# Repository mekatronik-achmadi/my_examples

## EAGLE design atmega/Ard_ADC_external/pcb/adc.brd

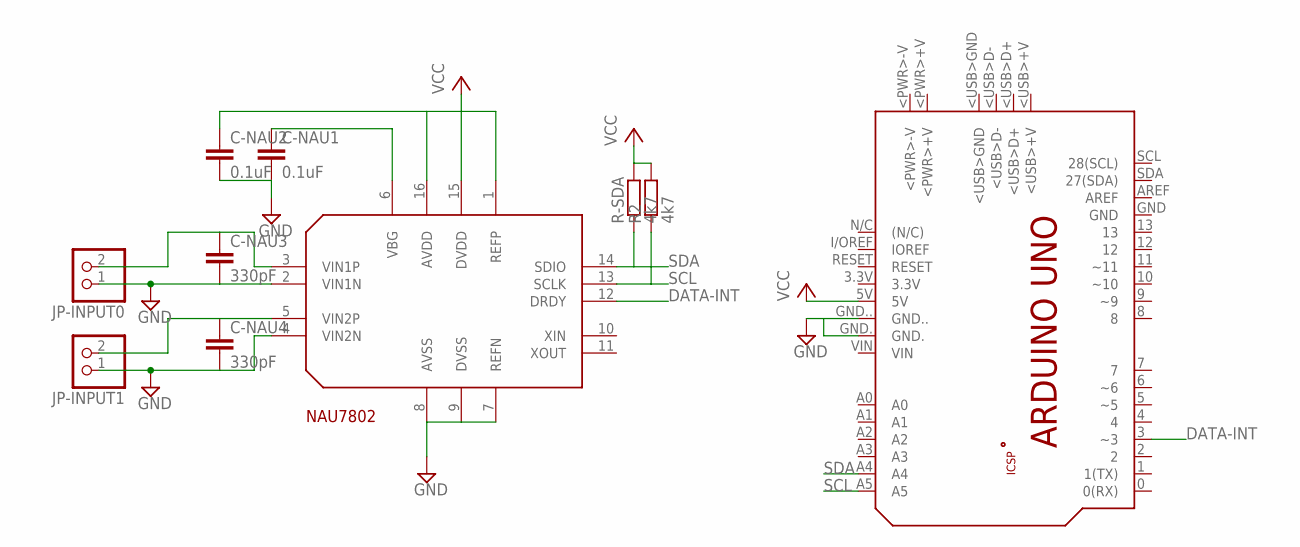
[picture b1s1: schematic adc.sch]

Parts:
C-NAU1, C-NAU2: 0.1uF; C050-024X044
C-NAU3, C-NAU4: 330pF; C050-024X044
JP-INPUT0, JP-INPUT1: PINHD-1X2; 1X02
PCB1: ARDUINO_UNO
R2: 4k7; 0204/7
R-SDA: 4k7; 0204/7
U$1: NAU7802_DIP; DIP16

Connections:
DATA-INT: PCB1.3 (~3), U$1.12 (DRDY)
GND: C-NAU1.2, C-NAU2.2, C-NAU3.2, C-NAU4.2, JP-INPUT0.1, JP-INPUT1.1, PCB1.GND., PCB1.GND.., U$1.2 (VIN1N), U$1.4 (VIN2N), U$1.7 (REFN), U$1.8 (AVSS), U$1.9 (DVSS)
unnamed: C-NAU1.1, U$1.6 (VBG)
unnamed: C-NAU3.1, JP-INPUT0.2, U$1.3 (VIN1P)
unnamed: C-NAU4.1, JP-INPUT1.2, U$1.5 (VIN2P)
SCL: PCB1.A5, R2.1, U$1.13 (SCLK)
SDA: PCB1.A4, R-SDA.1, U$1.14 (SDIO)
VCC: C-NAU2.1, PCB1.5V, R2.2, R-SDA.2, U$1.1 (REFP), U$1.15 (DVDD), U$1.16 (AVDD)

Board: 2 copper layers, 10 parts (0 on the bottom side), 8 nets, no tracks yet.

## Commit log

2018-10-09 some of my examples
2018-10-14 examples stm32 from rtm7777
2018-10-17 lcd library
2018-10-18 java android example
2018-10-20 Java Swing GUI example
2018-10-20 simple SysInfo on Java and Python
2018-10-22 java sysinfo
2018-10-23 blogspot template
2018-10-23 BT Serial Terminal
2018-10-23 gui example (Java and Qt)
2018-10-23 update examples
2018-10-30 document build helper scripts
2018-10-30 more doxygen config
2018-10-30 move to achmadi-default
2018-11-01 Fuzzy in C
2018-11-09 bashrc
2018-11-09 bashrc git
2018-11-10 some java and gtk examples
2018-11-13 mfc example
2018-11-18 win32 api
2018-11-18 win32 c example
2018-11-18 winegcc
2018-11-21 wine32 sys info
2018-11-21 win32 c
2018-11-21 win32 makefile
2018-11-22 win32 c and clean-up
2018-12-13 mingw makefile
2018-12-13 simulasi Fuzzy
2018-12-15 atmega mux
2018-12-17 stm32f103 web
2018-12-17 info, license, and documentation
2018-12-17 add gyro/accel
2018-12-17 rongsokan jalan
2018-12-18 jalan cuyy
2018-12-18 stm32 web mpu6050 prototype
2018-12-19 vector magnitude
2018-12-19 documentation using doxygen
2018-12-19 app copyright
2018-12-19 didin asu
2018-12-20 python ThorlabsPM100
2018-12-20 running as expected
2018-12-25 progress didin
2019-01-20 update WebADC
2019-03-18 re-use anbox
2019-03-21 lcd rpm
2019-03-26 ATMega Basic
2019-03-26 Makefile multi-platform
2019-03-27 basic ATMega examples
2019-03-27 No Simulide example
2019-03-31 on other lib
2019-03-31 face recog opencv
2019-03-31 face recoc opencv-python
2019-04-01 haarcascade flexible
2019-04-05 sim_proteus
2019-04-19 atmegaArduinoRPM
2019-04-21 face_rec analisa
2019-04-21 input capture
2019-04-21 period
2019-06-26 matlab batch run example
2019-07-03 deboat MIUI-10 scripts
2019-07-19 archived Face Recog Job
2019-07-19 example tiny sys-info
2019-07-19 development
2019-07-19 sh_info
2019-07-26 m128-fatfs_qt
2019-09-22 python keras
2019-09-28 minicona portable
2019-09-30 Java Android
2019-09-30 too slow
2019-10-06 ESP8266 esp-open-sdk
2019-10-06 esp8266 led and serial out
2019-10-07 esp8266 websocket
2019-10-07 test web change
2019-10-07 more esp8266 basic example
2019-10-18 conda
2019-10-18 android WebView
2019-10-18 switch default to duckduckgo
2019-10-18 big example for Android HTTP interface
2019-10-20 conda update
2019-10-24 default makefile no-need gpio_init()
2019-10-24 gpio_init() must called only once
2020-01-14 tes tnode/array
2020-01-14 repair whitespace
2020-04-10 personal components inventory
2020-05-14 esp8266 uart LED
2020-05-15 esp8266 http host-client
2020-05-17 esp8266 mosquitto client
2020-05-17 esp8266 mqtt subs
2020-06-06 esp8266 all led
2020-06-06 include fix
2020-06-15 tmux script example
2020-07-10 update miui debloat
2020-07-10 update debloat miui
2020-07-19 multibootusb
2020-08-10 tmux
2020-08-10 komponen
2020-10-13 c pointer
2020-12-22 stm32 ili94341
2020-12-22 stm32 ili9341
2020-12-22 bluepill ili9341
2020-12-22 nucleof4 ili9341
2020-12-24 seabreeze example
2020-12-24 esp8266 mqtt update
2021-01-06 heat transfer using GA
2021-01-07 mysql dbase python
2021-01-07 SQL python
2021-01-07 nucleo f4 exti
2021-01-14 crooked example
2021-01-17 cerdas cermat example
2021-01-22 STM32 Cube GCC
2021-01-26 flutter example
2021-02-08 wx Serial Terminal
2021-02-13 project moved
2021-03-02 vim commands
2021-03-04 car Optical Character Recognition
2021-03-16 apple selection test
2021-04-09 flutter serial
2021-04-09 flutter serial usb filter
2021-04-09 fluterr serial stm32 vcp
2021-04-19 some scripts
2021-05-28 pcb opto
2021-06-02 kwa_ellen
2021-06-13 some stupid example
2021-06-13 py examples
2021-07-07 basic gtk template
2021-07-07 update gtk template
2021-07-07 update gtk sh cmd
